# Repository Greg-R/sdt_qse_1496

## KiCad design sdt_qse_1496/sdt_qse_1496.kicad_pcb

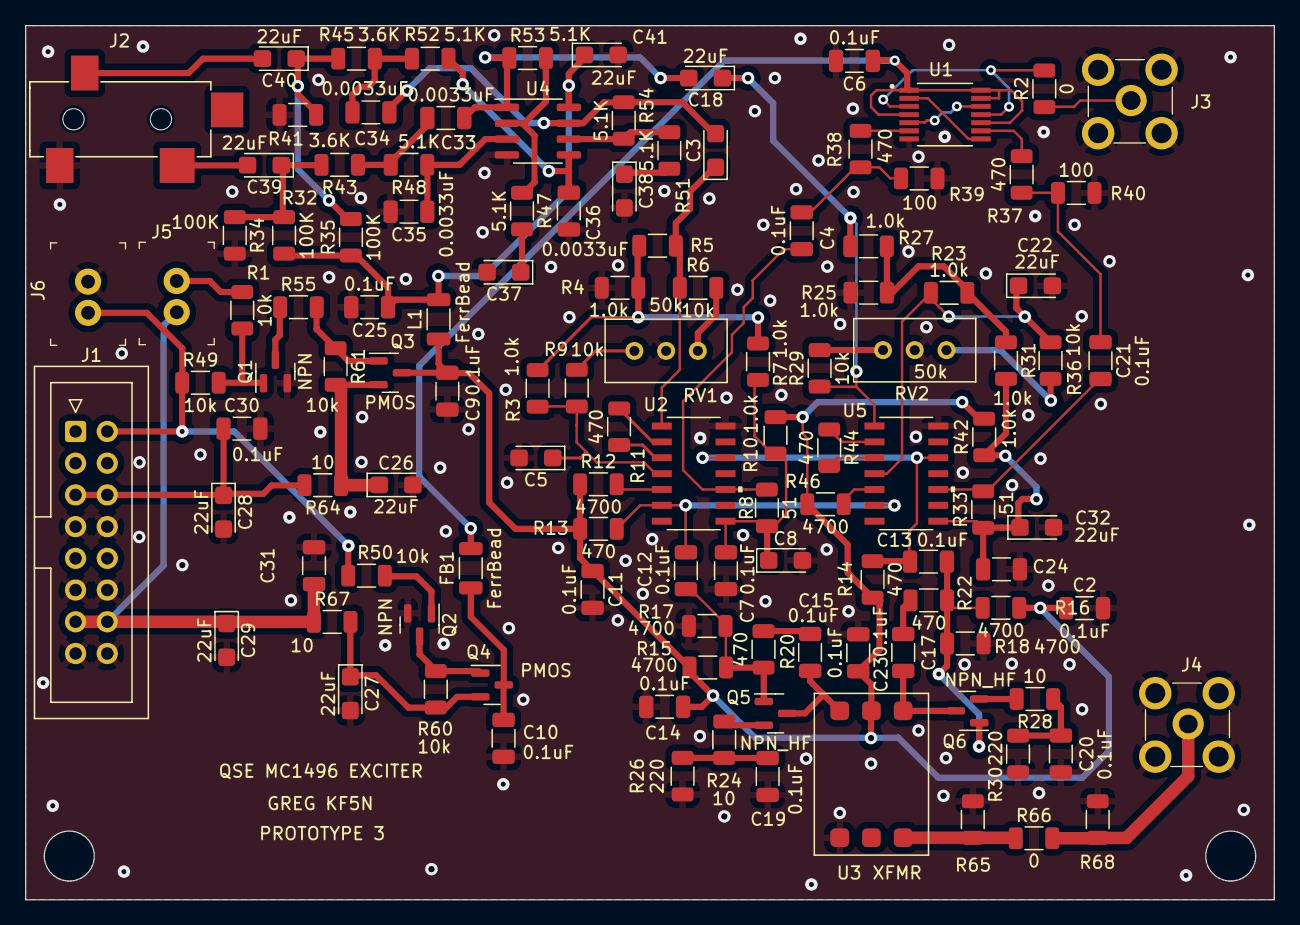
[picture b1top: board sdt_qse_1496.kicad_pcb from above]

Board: 2 copper layers, 100.0 x 70.0 mm, 120 parts (0 on the bottom side), 72 nets.

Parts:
C2, C4, C6, C7, C9, C10, C11, C12, C13, C14, C15, C17, C19, C20, C21, C23, C24, C25, C30, C31: 0.1uF; C_1206_3216Metric
C3, C5, C8, C18, C22, C26, C27, C28, C29, C32, C37, C38, C39, C40, C41: 22uF; CP_EIA-3216-10_Kemet-I
C33, C34, C35, C36: 0.0033uF; C_1206_3216Metric
FB1: FerrBead; L_1206_3216Metric
J1: Conn_02x08_Odd_Even; IDC-Header_2x08_P2.54mm_Vertical
J2: SJ-3524-SMT; CUI_SJ-3524-SMT
J3, J4: 5-1814832-1; RF_SMA_Vertical_5-1814832-1
J5, J6: Conn_01x02_Male; PinHeader_1x2_P2.5mm_Drill1.1mm
L1: FerrBead; L_1206_3216Metric
Q1, Q2: NPN; SOT-23
Q3, Q4: PMOS; SOT-23
Q5, Q6: NPN_HF; SOT-23
R1, R6, R9, R29, R36, R49, R50, R55, R60, R61: 10k; R_1206_3216Metric
R2, R66: 0; R_1206_3216Metric
R3, R4, R5, R7, R10, R23, R25, R27, R31, R42: 1.0k; R_1206_3216Metric
R8, R33: 51; R_1206_3216Metric
R11, R13, R14, R20, R22, R37, R38, R44: 470; R_1206_3216Metric
R12, R15, R16, R17, R18, R46: 4700; R_1206_3216Metric
R24, R28, R64, R67: 10; R_1206_3216Metric
R26, R30: 220; R_1206_3216Metric
R32, R34, R35, R41: 100K; R_1206_3216Metric
R39, R40: 100; R_1206_3216Metric
R43, R45: 3.6K; R_1206_3216Metric
R47, R48, R51, R52, R53, R54: 5.1K; R_1206_3216Metric
R65, R68: DNP; R_1206_3216Metric
RV1, RV2: 50k; Potentiometer_Bourns_3296W_Vertical
U1: SN74AC74PW; SOP65P640X120-14N
U2, U5: MC1496DR2G
U3: XFMR; Toroid_XFMR_SMD
U4: LM4562; SOIC-8_3.9x4.9mm_P1.27mm

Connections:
/3_3V: C29.1, C31.1, J1.13, J1.14, J5.1, R67.1
/3_3V_switched: C6.1, FB1.2, U1.1 (~1CLR), U1.4 (~1PRE), U1.10 (~2PRE), U1.13 (~2CLR), U1.14 (VCC)
/12V: C28.1, C30.1, J1.5, J1.6, R64.2
/12Vswitched: C2.1, C9.1, C11.1, C14.1, C23.2, L1.1, Q3.3 (D), R10.2, R12.1, R13.1, R14.1, R15.2, R16.2, R42.2, R46.1, U3.3
/Double Balanced Modulator1/baseband_in: C3.2, C34.1, R54.1, U4.7
/Double Balanced Modulator/baseband_in: C18.2, C33.1, R53.1, U4.1
/Double Balanced Modulator/outminus: C13.1, R14.2, U2.12 (OUTPUT), U5.12 (OUTPUT)
/Double Balanced Modulator/outplus: C12.1, R13.2, U2.6 (OUTPUT), U5.6 (OUTPUT)
/LO_NINETY: C4.1, R38.2, R39.2
/LO_ZERO: C21.1, R37.2, R40.2
/SallenKeyFilters/12V_AA: C25.1, C41.1, L1.2, R32.1, R35.1, U4.8 (V+)
/SallenKeyFilters/TX_RAW_I_IN: C39.2, J2.2
/SallenKeyFilters/TX_RAW_Q_IN: C40.2, J2.3
/TXRX: J1.2, J6.1, R49.1, R50.1
GND: C2.2, C5.2, C6.2, C7.2, C8.2, C9.2, C10.2, C11.2, C14.2, C19.1, C20.1, C22.2, C23.1, C24.2, C25.2, C26.2, C27.2, C28.2, C29.2, C30.2, C31.2, C32.2, C35.2, C36.2, C37.2, C38.2, C41.2, J1.7, J1.8, J1.11, J1.12, J1.15, J1.16, J2.1, J3.1, J4.1, J6.2, Q1.2 (E), Q2.2 (E), R4.1, R17.1, R18.1, R25.1, R26.1, R30.1, R34.2, R39.1, R40.1, R41.2, R65.1, R68.1, RV1.2, RV2.2, U1.7 (GND), U2.14 (VEE), U3.2, U4.4 (V-), U5.14 (VEE)
unnamed: C3.1, R5.2, R6.1, U2.1 (SIGNALINPUT)
unnamed: C5.1, R3.2, R9.1, U2.4 (SIGNALINPUT)
unnamed: C15.1, R20.1
unnamed: C17.1, R22.1
unnamed: C18.1, R27.2, R29.1, U5.1 (SIGNALINPUT)
unnamed: C19.2, R24.1, R26.2
unnamed: C20.2, R28.1, R30.2
unnamed: C22.1, R23.2, R36.1, U5.4 (SIGNALINPUT)
unnamed: C33.2, R43.1, R48.2
unnamed: C34.2, R45.1, R52.2
unnamed: C37.1, R47.2
unnamed: C38.1, R51.2
unnamed: C39.1, R32.2, R34.1, R43.2
unnamed: C40.1, R35.2, R41.1, R45.2
unnamed: J3.2, R2.1
unnamed: J4.2, R66.2, R68.2
unnamed: J5.2, R1.2
unnamed: Q1.1 (B), R1.1, R49.2
unnamed: Q1.3 (C), R55.1
unnamed: Q2.1 (B), R50.2
unnamed: Q2.3 (C), Q4.1 (G), R60.1
unnamed: Q3.1 (G), R55.2, R61.1
unnamed: C26.1, Q3.2 (S), R61.2, R64.1
unnamed: C10.1, FB1.1, Q4.3 (D)
unnamed: C27.1, Q4.2 (S), R60.2, R67.2
unnamed: C12.2, Q5.1 (B), R15.1, R17.2, R20.2
unnamed: C15.2, Q5.3 (C), U3.1
unnamed: Q5.2 (E), R24.2
unnamed: C13.2, Q6.1 (B), R16.1, R18.2, R22.2
unnamed: C17.2, Q6.3 (C), U3.5
unnamed: Q6.2 (E), R28.2
unnamed: R3.1, R4.2, R5.1, R7.1
unnamed: R6.2, RV1.3
unnamed: R9.2, RV1.1
unnamed: R11.1, U2.2 (GAINADJUST)
unnamed: R11.2, U2.3 (GAINADJUST)
unnamed: R23.1, R25.2, R27.1, R31.1
unnamed: R29.2, RV2.3
unnamed: R36.2, RV2.1
unnamed: R44.1, U5.2 (GAINADJUST)
unnamed: R44.2, U5.3 (GAINADJUST)
unnamed: R65.2, R66.1, U3.6
unnamed: R2.2, U1.3 (1CLK), U1.11 (2CLK)
unnamed: U1.2 (1D), U1.8 (~2Q)
unnamed: U1.5 (1Q), U1.12 (2D)
unnamed: R37.1, U1.9 (2Q)
unnamed: R38.1, U1.6 (~1Q)
unnamed: R12.2, U2.5 (BIAS)
unnamed: C4.2, R8.2, U2.10 (CARRIERINPUT)
unnamed: C7.1, C8.1, R7.2, R8.1, R10.1, U2.8 (INPUTCARRIER)
unnamed: C35.1, R48.1, U4.3 (+)
unnamed: R47.1, R53.2, U4.2 (-)
unnamed: C36.1, R52.1, U4.5 (+)
unnamed: R51.1, R54.2, U4.6 (-)
unnamed: R46.2, U5.5 (BIAS)
unnamed: C21.2, R33.2, U5.10 (CARRIERINPUT)
unnamed: C24.1, C32.1, R31.2, R33.1, R42.1, U5.8 (INPUTCARRIER)

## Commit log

2022-12-06 Initial commit, schematic complete.
2022-12-08 Layout mostly done. In review.
2022-12-10 Released to fab.
2022-12-28 More simulations working.
2023-01-10 Some improvements to the MC1496 simulations.
2023-01-17 Finishing layout of version2.
2023-01-17 Added gerbers for Prototype 2.
2023-01-27 Released version 2.0 PCB.
2023-03-14 New simulations added.
2023-03-15 Added Sallen Key filters to schematic.
2023-03-16 Almost ready to release Prototype 3.
2023-03-16 Checked gerbers, releasing to PCBWay.
2023-04-13 Commit before backup.
2023-04-13 Updated gitignore
2023-04-13 Clean up unused directories.
2024-03-31 Unknown commit.

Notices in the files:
parts and their libraries:
Copyright 2021 Accelerated Designs. All rights reserved.
